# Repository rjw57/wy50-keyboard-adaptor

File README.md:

# WY-50 PS/2 Keyboard Adaptor

Work in progress. Not yet ready.

## Getting interactive terminal

Use stdin for keyboard but show result on terminal:

sudo socat -d -d 'stdin,raw,echo=0!!/dev/ttyUSB0,b38400,raw,echo=0' exec:"/bin/login -f $USER TERM=wy50",pty,setsid,setpgid,stderr,ctty

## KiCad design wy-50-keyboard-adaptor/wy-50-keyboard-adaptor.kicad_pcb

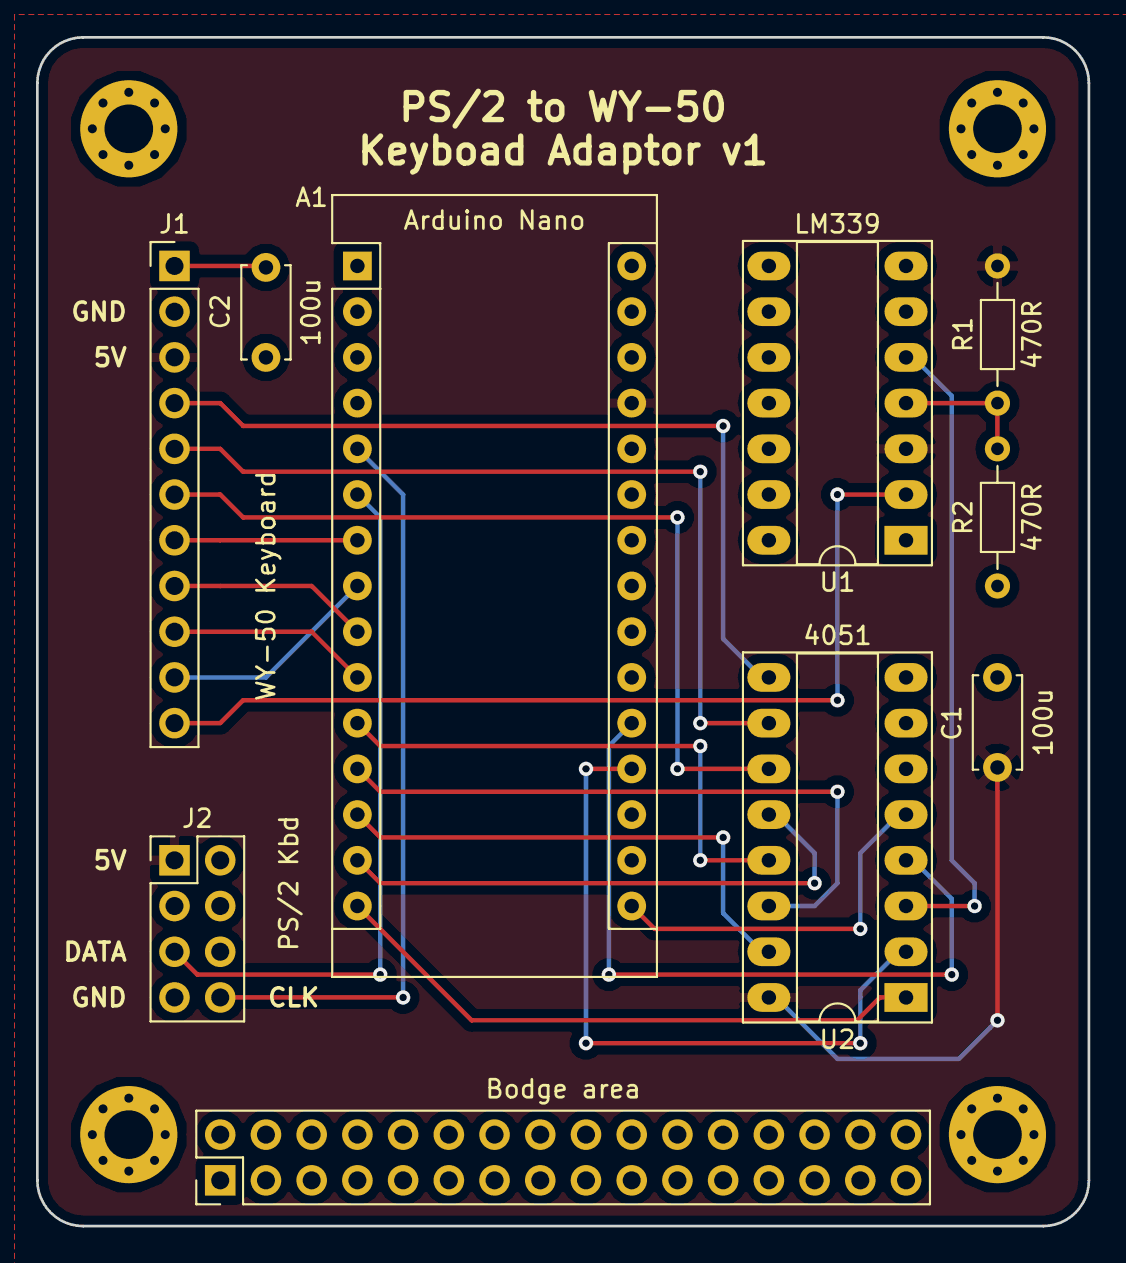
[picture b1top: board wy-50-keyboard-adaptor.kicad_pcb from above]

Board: 2 copper layers, 58.4 x 66.0 mm, 9 parts (0 on the bottom side), 23 nets.

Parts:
A1: Arduino Nano; Arduino_Nano
C1, C2: 100u; C_Disc_D5.0mm_W2.5mm_P5.00mm
J1: WY-50 Keyboard; PinHeader_1x11_P2.54mm_Vertical
J2: PS/2 Kbd; PinHeader_2x04_P2.54mm_Vertical
R1, R2: 470R; R_Axial_DIN0204_L3.6mm_D1.6mm_P7.62mm_Horizontal
U1: LM339; DIP-14_W7.62mm_Socket_LongPads
U2: 4051; DIP-16_W7.62mm_Socket_LongPads

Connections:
KBD1: C2.2, J1.1
KBD2: A1.4, A1.29, C1.1, C2.1, J1.2, J2.7, R2.1, U1.12, U2.6, U2.7, U2.8
KBD3: A1.27, C1.2, J1.3, J2.1, R1.2, U1.3, U2.16
KBD4: J1.4, U2.9
KBD5: J1.5, U2.10
KBD6: J1.6, U2.11
KBD7: A1.7, J1.7
KBD8: A1.9, J1.8
KBD9: A1.10, J1.9
KBD10: A1.8, J1.10
KBD11: J1.11, U1.2
unnamed: R1.1, R2.2, U1.4
unnamed: U1.5, U2.3
PS2CLK: A1.5, J2.8
PS2DATA: A1.6, J2.5
ROW0: A1.11, U2.13
ROW1: A1.12, U2.14
ROW2: A1.13, U2.15
ROW3: A1.14, U2.12
ROW4: A1.15, U2.1
ROW5: A1.16, U2.5
ROW6: A1.19, U2.2
ROW7: A1.20, U2.4

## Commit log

2021-12-20 initial import
2022-01-08 show socat magic
2022-01-08 add hardware
